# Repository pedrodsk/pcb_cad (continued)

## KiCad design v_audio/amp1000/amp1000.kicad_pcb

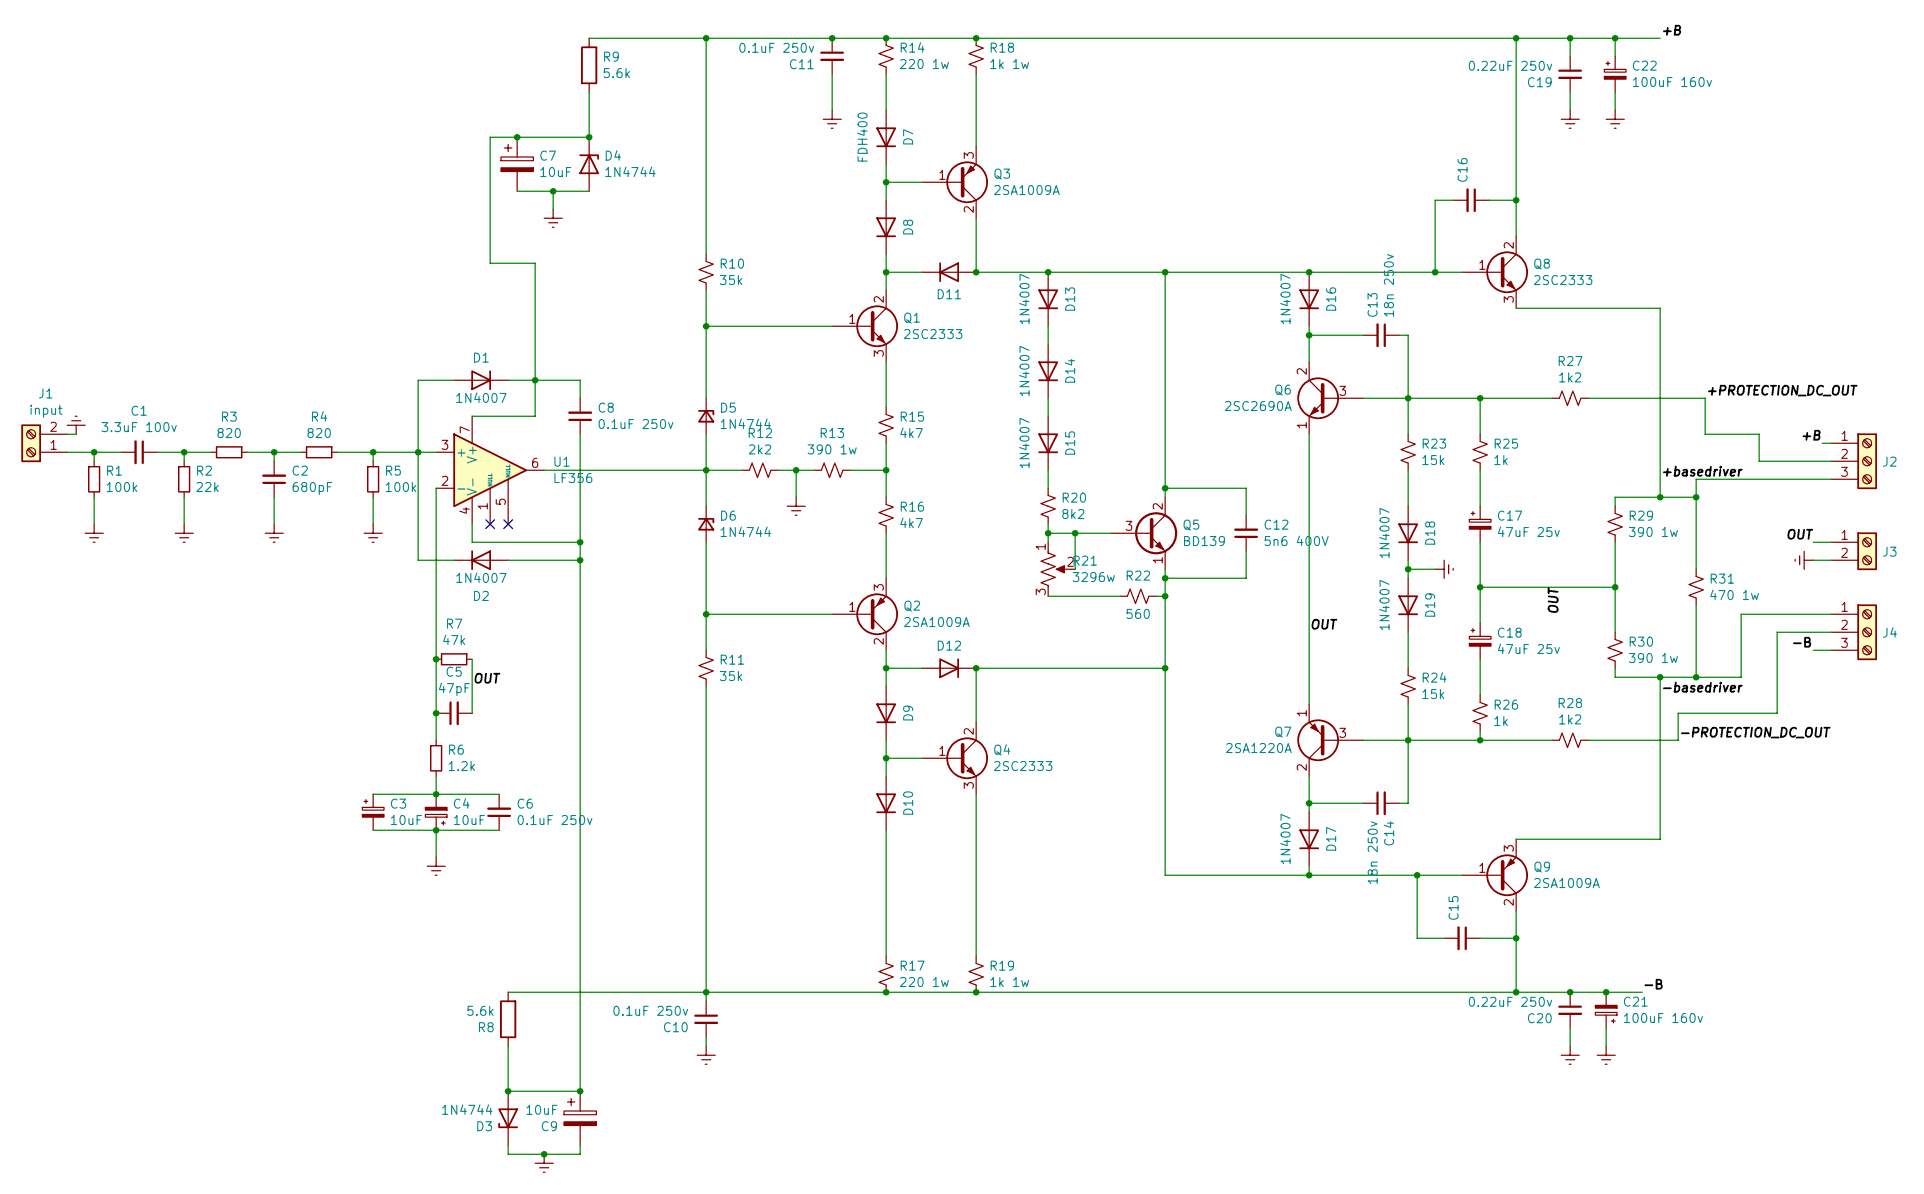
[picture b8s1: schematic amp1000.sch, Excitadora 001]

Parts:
C1: 3.3uF 100v; C_Axial_L22.0mm_D9.5mm_P27.50mm_Horizontal
C2: 680pF; C_Disc_D5.0mm_W2.5mm_P5.00mm
C3, C4, C7, C9: 10uF; CP_Radial_D4.0mm_P2.00mm
C5: 47pF; C_Disc_D5.0mm_W2.5mm_P5.00mm
C6, C8: 0.1uF 250v; C_Disc_D5.0mm_W2.5mm_P5.00mm
C10, C11: 0.1uF 250v; C_Disc_D7.5mm_W5.0mm_P10.00mm
C12: 5n6 400V; C_Disc_D5.0mm_W2.5mm_P5.00mm
C13, C14: 18n 250v; C_Disc_D5.0mm_W2.5mm_P5.00mm
C15, C16: 0.22uF 250v; C_Disc_D5.0mm_W2.5mm_P5.00mm
C17, C18: 47uF 25v; CP_Radial_D8.0mm_P3.50mm
C19, C20: 0.22uF 250v; C_Disc_D7.5mm_W5.0mm_P10.00mm
C21, C22: 100uF 160v; CP_Radial_D10.0mm_P5.00mm
D1, D2, D8, D9, D10, D11, D12, D13, D14, D15, D16, D17, D18, D19: 1N4007; D_A-405_P7.62mm_Horizontal
D3, D4, D5, D6: 1N4744; D_A-405_P7.62mm_Horizontal
D7: FDH400; D_A-405_P7.62mm_Horizontal
J1: input; TerminalBlock_bornier-2_P5.08mm
J2, J4: Screw_Terminal_01x03; TerminalBlock_bornier-3_P5.08mm
J3: Screw_Terminal_01x02; TerminalBlock_bornier-2_P5.08mm
Q1, Q4: 2SC2333; TO-220-3_Vertical
Q2, Q3: 2SA1009A; TO-220-3_Vertical
Q5: BD139; TO-126-3_Vertical
Q6: 2SC2690A; TO-126-3_Vertical
Q7: 2SA1220A; TO-126-3_Vertical
Q8: 2SC2333; TO-220-3_Horizontal_TabDown
Q9: 2SA1009A; TO-220-3_Horizontal_TabDown
R1, R5: 100k; R_Axial_DIN0207_L6.3mm_D2.5mm_P7.62mm_Horizontal
R2: 22k; R_Axial_DIN0207_L6.3mm_D2.5mm_P7.62mm_Horizontal
R3, R4: 820; R_Axial_DIN0207_L6.3mm_D2.5mm_P7.62mm_Horizontal
R6: 1.2k; R_Axial_DIN0207_L6.3mm_D2.5mm_P7.62mm_Horizontal
R7: 47k; R_Axial_DIN0207_L6.3mm_D2.5mm_P7.62mm_Horizontal
R8, R9: 5.6k; R_Axial_DIN0207_L6.3mm_D2.5mm_P7.62mm_Horizontal
R10, R11: 35k; R_Axial_DIN0207_L6.3mm_D2.5mm_P7.62mm_Horizontal
R12: 2k2; R_Axial_DIN0207_L6.3mm_D2.5mm_P7.62mm_Horizontal
R13, R29, R30: 390 1w; R_Axial_DIN0207_L6.3mm_D2.5mm_P7.62mm_Horizontal
R14, R17: 220 1w; R_Axial_DIN0207_L6.3mm_D2.5mm_P7.62mm_Horizontal
R15, R16: 4k7; R_Axial_DIN0207_L6.3mm_D2.5mm_P7.62mm_Horizontal
R18, R19: 1k 1w; R_Axial_DIN0207_L6.3mm_D2.5mm_P7.62mm_Horizontal
R20: 8k2; R_Axial_DIN0207_L6.3mm_D2.5mm_P7.62mm_Horizontal
R21: 3296w; Potentiometer_Bourns_3296W_Vertical
R22: 560; R_Axial_DIN0207_L6.3mm_D2.5mm_P7.62mm_Horizontal
R23, R24: 15k; R_Axial_DIN0207_L6.3mm_D2.5mm_P7.62mm_Horizontal
R25, R26: 1k; R_Axial_DIN0207_L6.3mm_D2.5mm_P7.62mm_Horizontal
R27, R28: 1k2; R_Axial_DIN0207_L6.3mm_D2.5mm_P7.62mm_Horizontal
R31: 470 1w; R_Axial_DIN0207_L6.3mm_D2.5mm_P7.62mm_Horizontal
U1: LF356; DIP-8_W7.62mm

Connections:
/+B: C11.1, C16.1, C19.1, C22.1, J2.1, Q8.2 (C), R9.1, R10.2, R14.2, R18.2
/+PROTECTION_DC_OUT: J2.2, R27.2
/+basedriver: J2.3, Q8.3 (E), R29.2, R31.2
/-B: C10.1, C15.1, C20.1, C21.2, J4.3, Q9.2 (C), R8.2, R11.1, R17.1, R19.1
/-PROTECTION_DC_OUT: J4.2, R28.2
/-basedriver: J4.1, Q9.3 (E), R30.1, R31.1
/OUT: C5.2, C17.2, C18.1, J3.1, Q6.1 (E), Q7.1 (E), R7.1, R29.1, R30.2
Earth: C2.1, C3.2, C4.1, C6.1, C7.2, C9.2, C10.2, C11.2, C19.2, C20.2, C21.1, C22.2, D3.1 (K), D4.2 (A), D18.1 (K), D19.2 (A), J1.2, J3.2, R1.2, R2.2, R5.2, R12.1, R13.2
unnamed: C1.1, R2.1, R3.2
unnamed: C1.2, J1.1, R1.1
unnamed: C2.2, R3.1, R4.2
unnamed: C3.1, C4.2, C6.2, R6.2
unnamed: C5.1, R6.1, R7.2, U1.2 (-)
unnamed: C7.1, C8.2, D1.1 (K), D4.1 (K), R9.2, U1.7 (V+)
unnamed: C8.1, C9.1, D2.2 (A), D3.2 (A), R8.1, U1.4 (V-)
unnamed: C12.1, C15.2, D12.1 (K), D17.1 (K), Q4.2 (C), Q5.1 (E), Q9.1 (B), R22.1
unnamed: C12.2, C16.2, D11.2 (A), D13.2 (A), D16.2 (A), Q3.2 (C), Q5.2 (C), Q8.1 (B)
unnamed: C13.1, Q6.3 (B), R23.2, R25.2, R27.1
unnamed: C13.2, D16.1 (K), Q6.2 (C)
unnamed: C14.1, D17.2 (A), Q7.2 (C)
unnamed: C14.2, Q7.3 (B), R24.1, R26.1, R28.1
unnamed: C17.1, R25.1
unnamed: C18.2, R26.2
unnamed: D1.2 (A), D2.1 (K), R4.1, R5.1, U1.3 (+)
unnamed: D5.1 (K), Q1.1 (B), R10.1
unnamed: D5.2 (A), D6.1 (K), R12.2, U1.6
unnamed: D6.2 (A), Q2.1 (B), R11.2
unnamed: D7.1 (K), D8.2 (A), Q3.1 (B)
unnamed: D7.2 (A), R14.1
unnamed: D10.1 (K), R17.2
unnamed: D9.1 (K), D10.2 (A), Q4.1 (B)
unnamed: D8.1 (K), D11.1 (K), Q1.2 (C)
unnamed: D9.2 (A), D12.2 (A), Q2.2 (C)
unnamed: D13.1 (K), D14.2 (A)
unnamed: D14.1 (K), D15.2 (A)
unnamed: D15.1 (K), R20.2
unnamed: D18.2 (A), R23.1
unnamed: D19.1 (K), R24.2
unnamed: Q1.3 (E), R15.2
unnamed: Q2.3 (E), R16.1
unnamed: Q3.3 (E), R18.1
unnamed: Q4.3 (E), R19.2
unnamed: Q5.3 (B), R20.1, R21.1, R21.2
unnamed: R13.1, R15.1, R16.2
unnamed: R21.3, R22.2

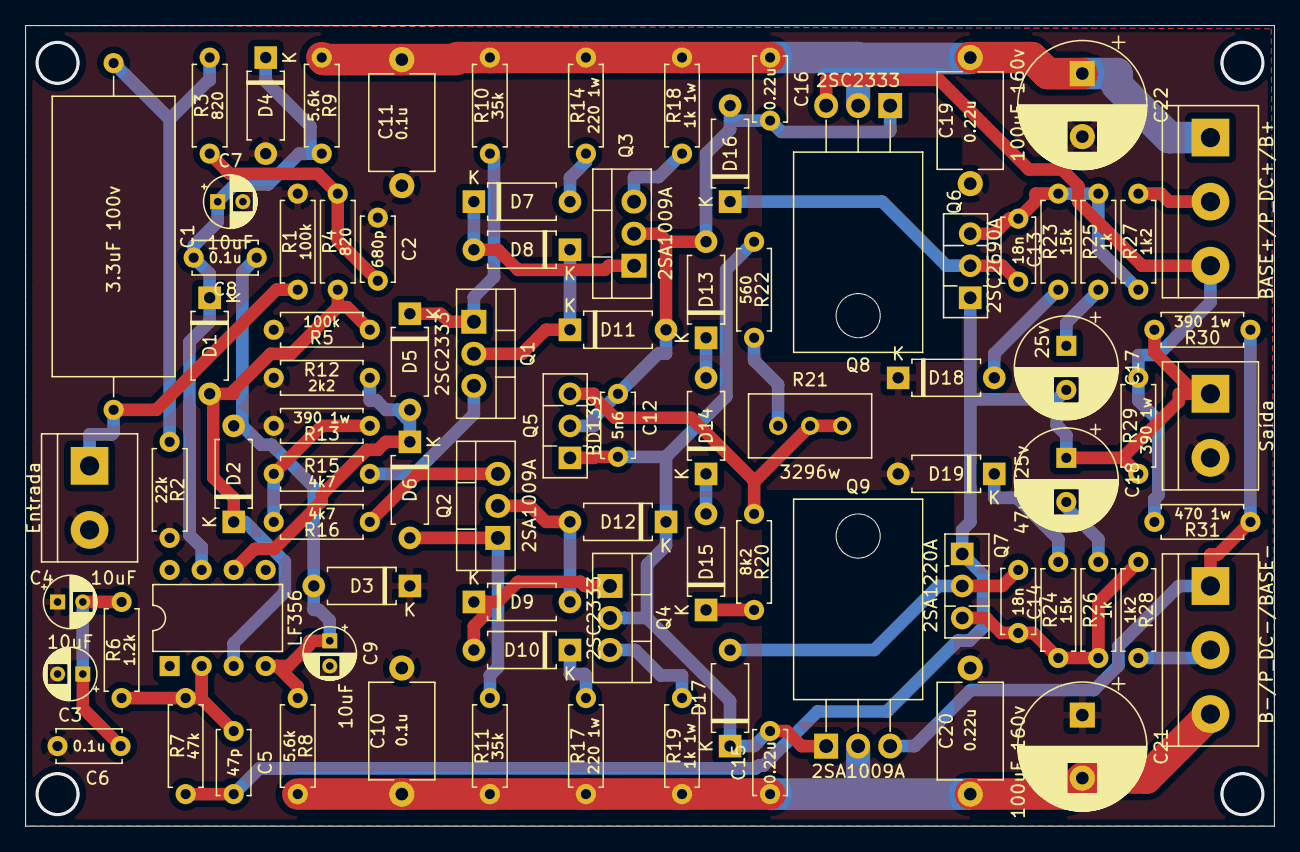
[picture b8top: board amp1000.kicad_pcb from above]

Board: 2 copper layers, 99.1 x 63.5 mm, 86 parts (0 on the bottom side), 45 nets.

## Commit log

2021-12-06 Old Projects
